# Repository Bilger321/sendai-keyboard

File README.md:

# sendai-keyboard
Just a little pet project of mine. Made using kiCAD.

Made with help from https://github.com/ruiqimao/keyboard-pcb-guide

Layout help was made with https://github.com/mechkeys/mechkeys

Code generated with http://kbfirmware.com/

Special Thanks to Jack @ https://github.com/qmk/qmk_firmware

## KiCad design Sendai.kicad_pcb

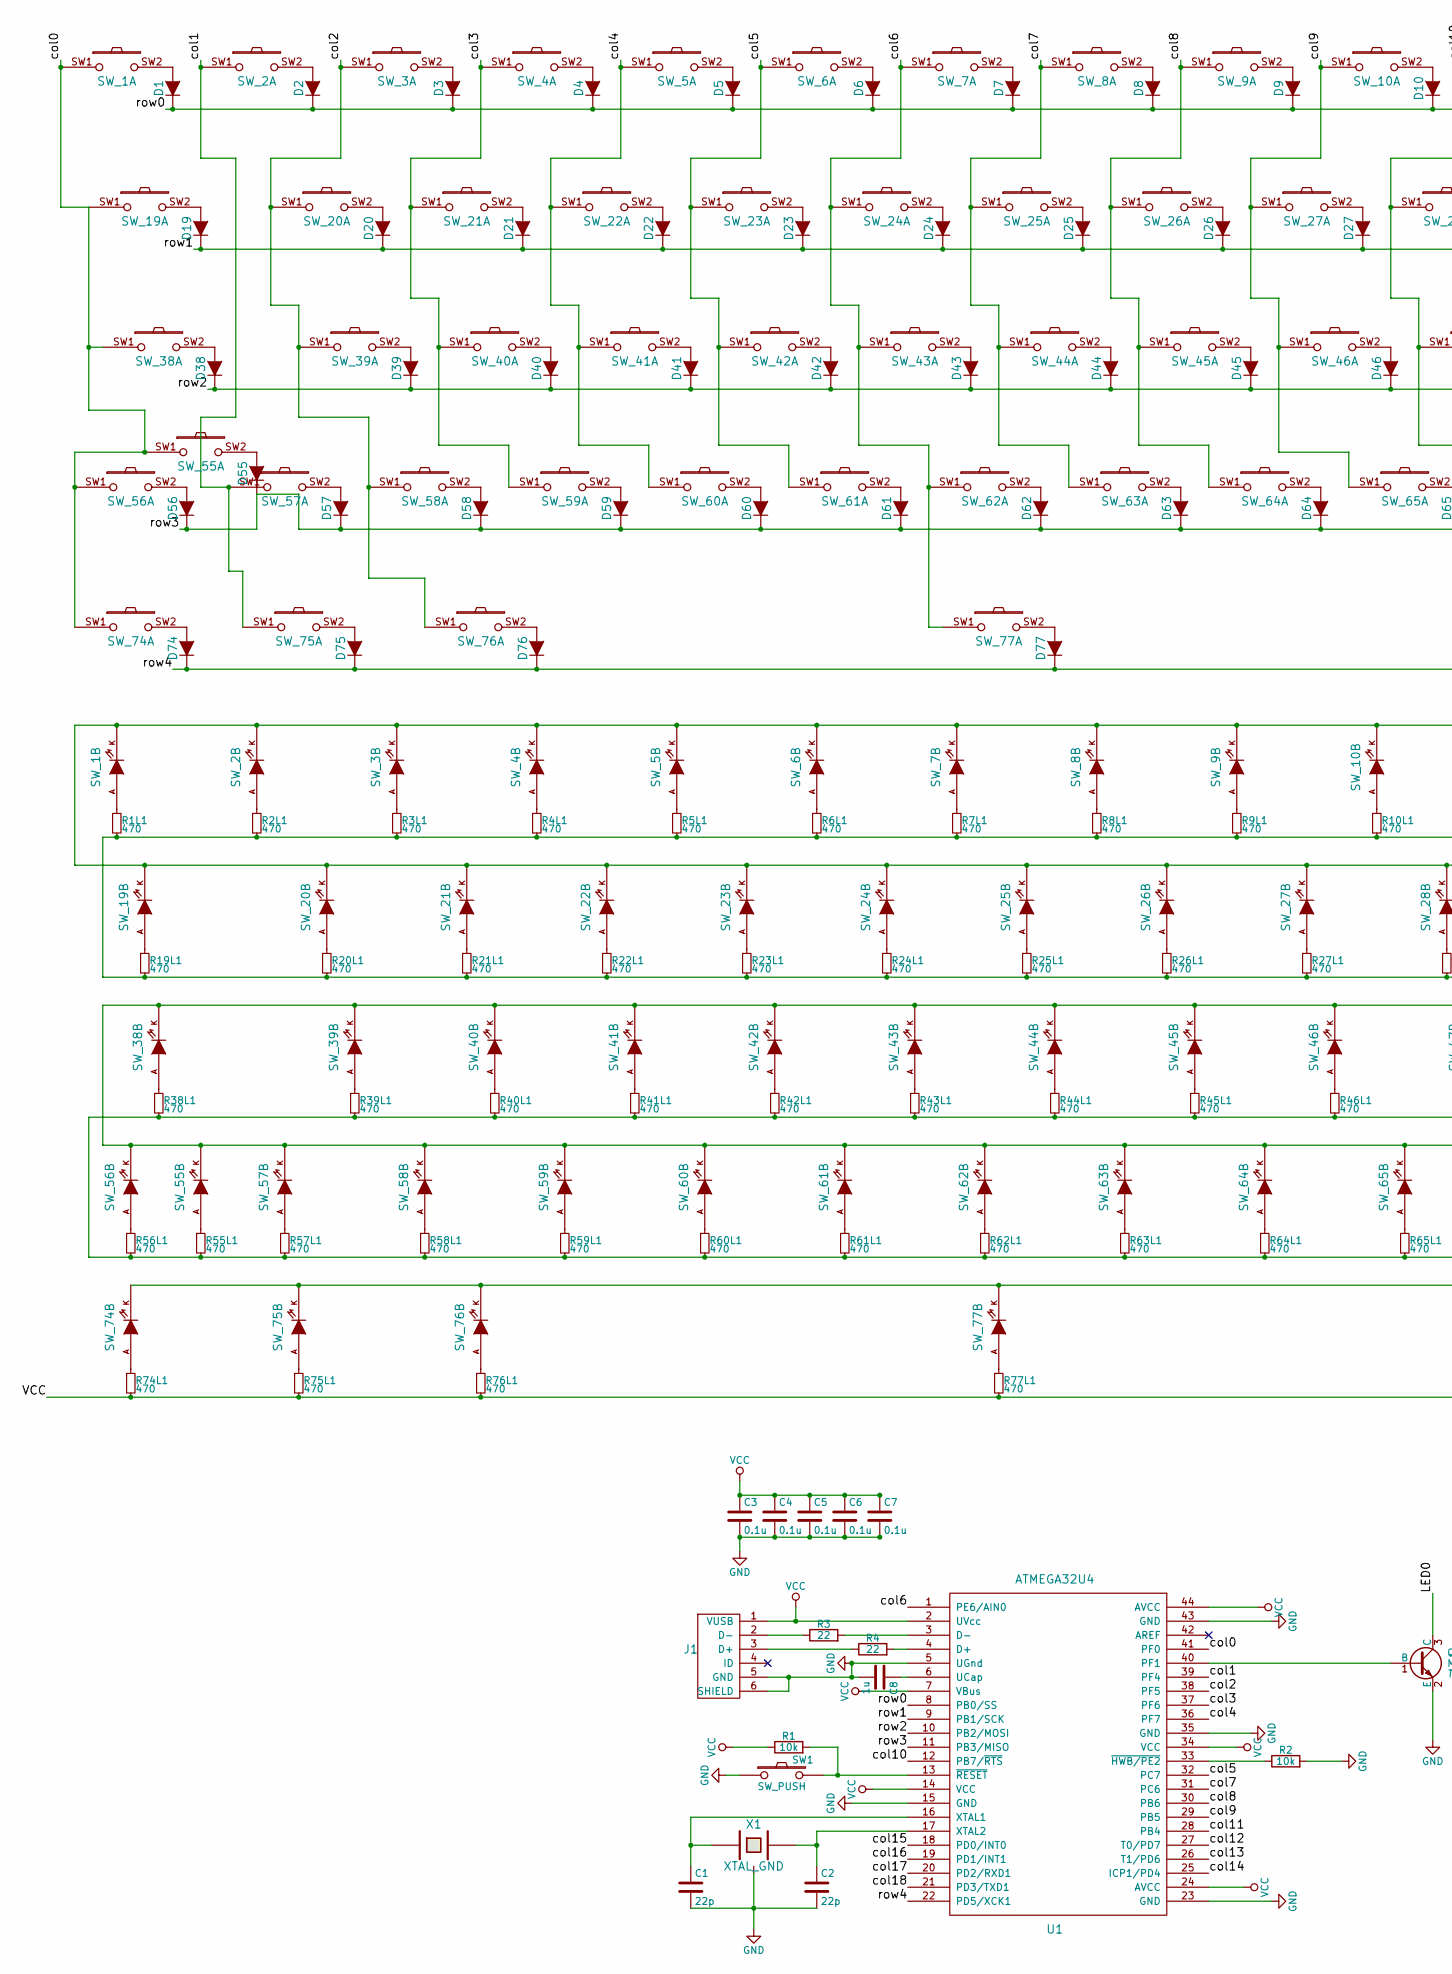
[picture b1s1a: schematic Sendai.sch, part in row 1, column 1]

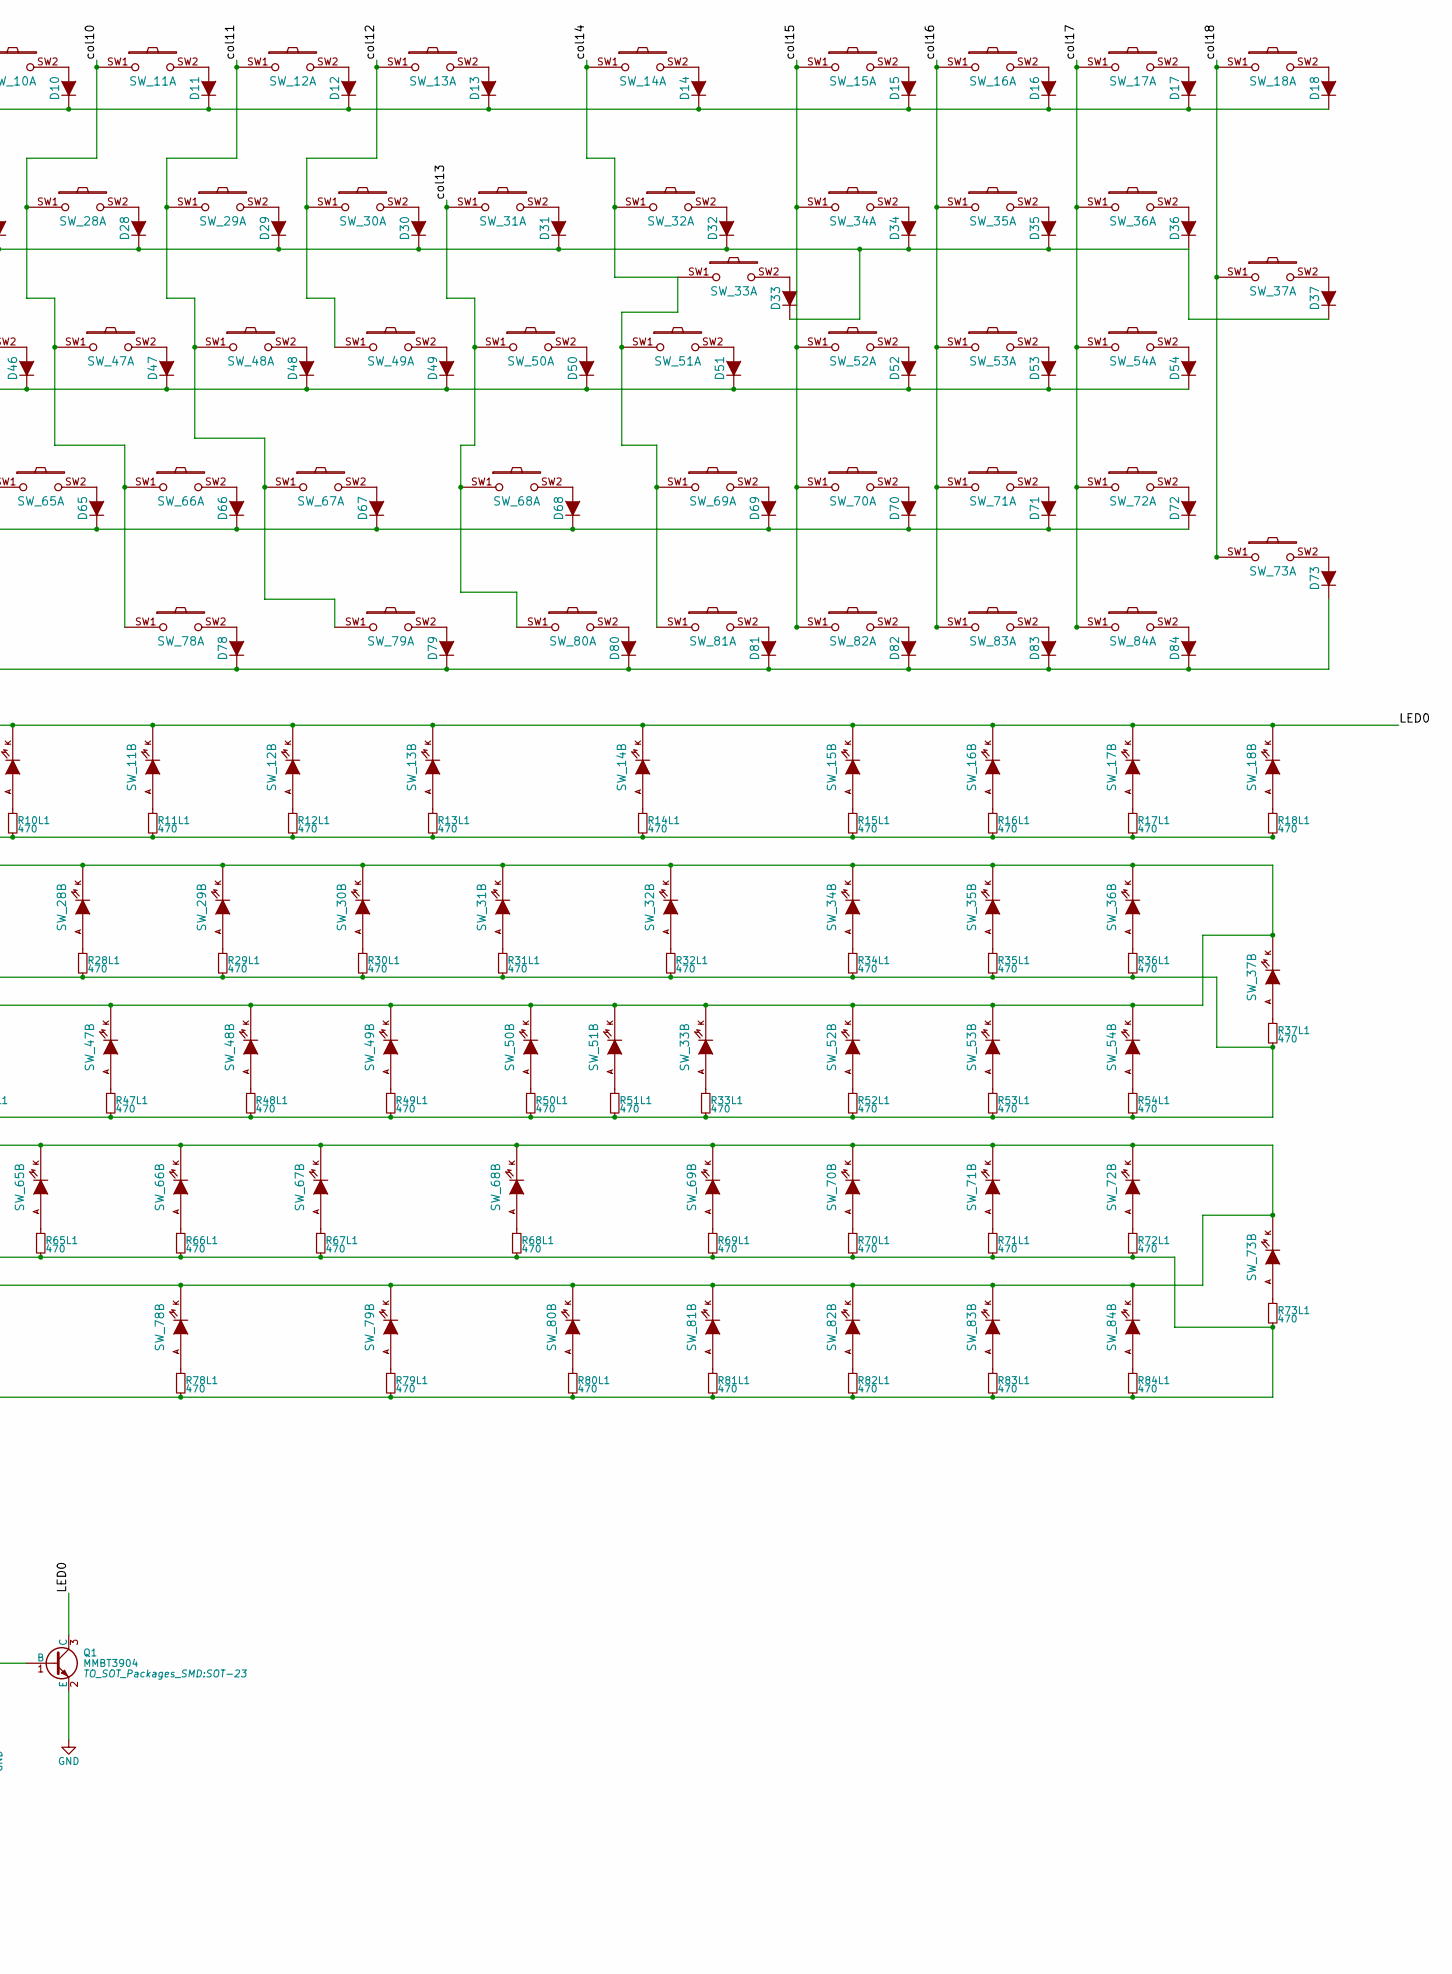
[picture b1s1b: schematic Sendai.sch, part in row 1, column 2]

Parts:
C1, C2: 22p; C_0805_HandSoldering
C3, C4, C5, C6, C7: 0.1u; C_0805_HandSoldering
C8: 1u; C_0805_HandSoldering
D1, D2, D3, D4, D5, D6, D7, D8, D9, D10, D11, D12, D13, D14, D15, D16, D17, D18, D19, D20, D21, D22, D23, D24, D25, D26, D27, D28, D29, D30, D31, D32, D33, D34, D35, D36, D37, D38, D39, D40, D41, D42, D43, D44, D45, D46, D47, D48, D49, D50, D51, D52, D53, D54, D55, D56, D57, D58, D59, D60, D61, D62, D63, D64, D65, D66, D67, D68, D69, D70, D71, D72, D73, D74, D75, D76, D77, D78, D79, D80, D81, D82, D83, D84: D; D_SOD123
J1: USB_mini_micro_B; USB_miniB_hirose_5S8
Q1: MMBT3904; SOT-23
R1, R2: 10k; R_0805_HandSoldering
R1L1, R2L1, R3L1, R4L1, R5L1, R6L1, R7L1, R8L1, R9L1, R10L1, R11L1, R12L1, R13L1, R14L1, R15L1, R16L1, R17L1, R18L1, R19L1, R20L1, R21L1, R22L1, R23L1, R24L1, R25L1, R26L1, R27L1, R28L1, R29L1, R30L1, R31L1, R32L1, R33L1, R34L1, R35L1, R36L1, R37L1, R38L1, R39L1, R40L1, R41L1, R42L1, R43L1, R44L1, R45L1, R46L1, R47L1, R48L1, R49L1, R50L1, R51L1, R52L1, R53L1, R54L1, R55L1, R56L1, R57L1, R58L1, R59L1, R60L1, R61L1, R62L1, R63L1, R64L1, R65L1, R66L1, R67L1, R68L1, R69L1, R70L1, R71L1, R72L1, R73L1, R74L1, R75L1, R76L1, R77L1, R78L1, R79L1, R80L1, R81L1, R82L1, R83L1, R84L1: 470; R_0805_HandSoldering
R3, R4: 22; R_0805_HandSoldering
SW1: SW_PUSH; SW_SPST_TL3342
SW_1, SW_2, SW_3, SW_4, SW_5, SW_6, SW_7, SW_8, SW_9, SW_10, SW_11, SW_12, SW_13, SW_14, SW_15, SW_16, SW_17, SW_18, SW_19, SW_20, SW_21, SW_22, SW_23, SW_24, SW_25, SW_26, SW_27, SW_28, SW_29, SW_30, SW_31, SW_32, SW_33, SW_34, SW_35, SW_36, SW_37, SW_38, SW_39, SW_40, SW_41, SW_42, SW_43, SW_44, SW_45, SW_46, SW_47, SW_48, SW_49, SW_50, SW_51, SW_52, SW_53, SW_54, SW_55, SW_56, SW_57, SW_58, SW_59, SW_60, SW_61, SW_62, SW_63, SW_64, SW_65, SW_66, SW_67, SW_68, SW_69, SW_70, SW_71, SW_72, SW_73, SW_74, SW_75, SW_76, SW_77, SW_78, SW_79, SW_80, SW_81, SW_82, SW_83, SW_84: MX_LED
U1: ATMEGA32U4; TQFP-44_10x10mm_Pitch0.8mm
X1: XTAL_GND; FA-238

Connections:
/LED0: Q1.3 (C), SW_1.K, SW_2.K, SW_3.K, SW_4.K, SW_5.K, SW_6.K, SW_7.K, SW_8.K, SW_9.K, SW_10.K, SW_11.K, SW_12.K, SW_13.K, SW_14.K, SW_15.K, SW_16.K, SW_17.K, SW_18.K, SW_19.K, SW_20.K, SW_21.K, SW_22.K, SW_23.K, SW_24.K, SW_25.K, SW_26.K, SW_27.K, SW_28.K, SW_29.K, SW_30.K, SW_31.K, SW_32.K, SW_33.K, SW_34.K, SW_35.K, SW_36.K, SW_37.K, SW_38.K, SW_39.K, SW_40.K, SW_41.K, SW_42.K, SW_43.K, SW_44.K, SW_45.K, SW_46.K, SW_47.K, SW_48.K, SW_49.K, SW_50.K, SW_51.K, SW_52.K, SW_53.K, SW_54.K, SW_55.K, SW_56.K, SW_57.K, SW_58.K, SW_59.K, SW_60.K, SW_61.K, SW_62.K, SW_63.K, SW_64.K, SW_65.K, SW_66.K, SW_67.K, SW_68.K, SW_69.K, SW_70.K, SW_71.K, SW_72.K, SW_73.K, SW_74.K, SW_75.K, SW_76.K, SW_77.K, SW_78.K, SW_79.K, SW_80.K, SW_81.K, SW_82.K, SW_83.K, SW_84.K
/col0: SW_1.SW1, SW_19.SW1, SW_38.SW1, SW_55.SW1, SW_56.SW1, SW_74.SW1, U1.41 (PF0)
/col1: SW_2.SW1, SW_57.SW1, SW_75.SW1, U1.39 (PF4)
/col2: SW_3.SW1, SW_20.SW1, SW_39.SW1, SW_58.SW1, SW_76.SW1, U1.38 (PF5)
/col3: SW_4.SW1, SW_21.SW1, SW_40.SW1, SW_59.SW1, U1.37 (PF6)
/col4: SW_5.SW1, SW_22.SW1, SW_41.SW1, SW_60.SW1, U1.36 (PF7)
/col5: SW_6.SW1, SW_23.SW1, SW_42.SW1, SW_61.SW1, U1.32 (PC7)
/col6: SW_7.SW1, SW_24.SW1, SW_43.SW1, SW_62.SW1, SW_77.SW1, U1.1 (PE6/AIN0)
/col7: SW_8.SW1, SW_25.SW1, SW_44.SW1, SW_63.SW1, U1.31 (PC6)
/col8: SW_9.SW1, SW_26.SW1, SW_45.SW1, SW_64.SW1, U1.30 (PB6)
/col9: SW_10.SW1, SW_27.SW1, SW_46.SW1, SW_65.SW1, U1.29 (PB5)
/col10: SW_11.SW1, SW_28.SW1, SW_47.SW1, SW_66.SW1, SW_78.SW1, U1.12 (PB7/~RTS)
/col11: SW_12.SW1, SW_29.SW1, SW_48.SW1, SW_67.SW1, SW_79.SW1, U1.28 (PB4)
/col12: SW_13.SW1, SW_30.SW1, SW_49.SW1, U1.27 (T0/PD7)
/col13: SW_31.SW1, SW_50.SW1, SW_68.SW1, SW_80.SW1, U1.26 (T1/PD6)
/col14: SW_14.SW1, SW_32.SW1, SW_33.SW1, SW_51.SW1, SW_69.SW1, SW_81.SW1, U1.25 (ICP1/PD4)
/col15: SW_15.SW1, SW_34.SW1, SW_52.SW1, SW_70.SW1, SW_82.SW1, U1.18 (PD0/INT0)
/col16: SW_16.SW1, SW_35.SW1, SW_53.SW1, SW_71.SW1, SW_83.SW1, U1.19 (PD1/INT1)
/col17: SW_17.SW1, SW_36.SW1, SW_54.SW1, SW_72.SW1, SW_84.SW1, U1.20 (PD2/RXD1)
/col18: SW_18.SW1, SW_37.SW1, SW_73.SW1, U1.21 (PD3/TXD1)
/row0: D1.1 (K), D2.1 (K), D3.1 (K), D4.1 (K), D5.1 (K), D6.1 (K), D7.1 (K), D8.1 (K), D9.1 (K), D10.1 (K), D11.1 (K), D12.1 (K), D13.1 (K), D14.1 (K), D15.1 (K), D16.1 (K), D17.1 (K), D18.1 (K), U1.8 (PB0/SS)
/row1: D19.1 (K), D20.1 (K), D21.1 (K), D22.1 (K), D23.1 (K), D24.1 (K), D25.1 (K), D26.1 (K), D27.1 (K), D28.1 (K), D29.1 (K), D30.1 (K), D31.1 (K), D32.1 (K), D33.1 (K), D34.1 (K), D35.1 (K), D36.1 (K), D37.1 (K), U1.9 (PB1/SCK)
/row2: D38.1 (K), D39.1 (K), D40.1 (K), D41.1 (K), D42.1 (K), D43.1 (K), D44.1 (K), D45.1 (K), D46.1 (K), D47.1 (K), D48.1 (K), D49.1 (K), D50.1 (K), D51.1 (K), D52.1 (K), D53.1 (K), D54.1 (K), U1.10 (PB2/MOSI)
/row3: D55.1 (K), D56.1 (K), D57.1 (K), D58.1 (K), D59.1 (K), D60.1 (K), D61.1 (K), D62.1 (K), D63.1 (K), D64.1 (K), D65.1 (K), D66.1 (K), D67.1 (K), D68.1 (K), D69.1 (K), D70.1 (K), D71.1 (K), D72.1 (K), U1.11 (PB3/MISO)
/row4: D73.1 (K), D74.1 (K), D75.1 (K), D76.1 (K), D77.1 (K), D78.1 (K), D79.1 (K), D80.1 (K), D81.1 (K), D82.1 (K), D83.1 (K), D84.1 (K), U1.22 (PD5/XCK1)
GND: C1.2, C2.2, C3.2, C4.2, C5.2, C6.2, C7.2, C8.2, J1.5 (GND), J1.6 (SHIELD), Q1.2 (E), R2.2, SW1.1, U1.5 (UGnd), U1.15 (GND), U1.23 (GND), U1.35 (GND), U1.43 (GND), X1.3
unnamed: C1.1, U1.16 (XTAL1), X1.1
unnamed: C2.1, U1.17 (XTAL2), X1.2
unnamed: C8.1, U1.6 (UCap)
unnamed: D1.2 (A), SW_1.SW2
unnamed: D2.2 (A), SW_2.SW2
unnamed: D3.2 (A), SW_3.SW2
unnamed: D4.2 (A), SW_4.SW2
unnamed: D5.2 (A), SW_5.SW2
unnamed: D6.2 (A), SW_6.SW2
unnamed: D7.2 (A), SW_7.SW2
unnamed: D8.2 (A), SW_8.SW2
unnamed: D9.2 (A), SW_9.SW2
unnamed: D10.2 (A), SW_10.SW2
unnamed: D11.2 (A), SW_11.SW2
unnamed: D12.2 (A), SW_12.SW2
unnamed: D13.2 (A), SW_13.SW2
unnamed: D14.2 (A), SW_14.SW2
unnamed: D15.2 (A), SW_15.SW2
unnamed: D16.2 (A), SW_16.SW2
unnamed: D17.2 (A), SW_17.SW2
unnamed: D18.2 (A), SW_18.SW2
unnamed: D19.2 (A), SW_19.SW2
unnamed: D20.2 (A), SW_20.SW2
unnamed: D21.2 (A), SW_21.SW2
unnamed: D22.2 (A), SW_22.SW2
unnamed: D23.2 (A), SW_23.SW2
unnamed: D24.2 (A), SW_24.SW2
unnamed: D25.2 (A), SW_25.SW2
unnamed: D26.2 (A), SW_26.SW2
unnamed: D27.2 (A), SW_27.SW2
unnamed: D28.2 (A), SW_28.SW2
unnamed: D29.2 (A), SW_29.SW2
unnamed: D30.2 (A), SW_30.SW2
unnamed: D31.2 (A), SW_31.SW2
unnamed: D32.2 (A), SW_32.SW2
unnamed: D33.2 (A), SW_33.SW2
unnamed: D34.2 (A), SW_34.SW2
unnamed: D35.2 (A), SW_35.SW2
unnamed: D36.2 (A), SW_36.SW2
unnamed: D37.2 (A), SW_37.SW2
unnamed: D38.2 (A), SW_38.SW2
unnamed: D39.2 (A), SW_39.SW2
unnamed: D40.2 (A), SW_40.SW2
unnamed: D41.2 (A), SW_41.SW2
unnamed: D42.2 (A), SW_42.SW2
unnamed: D43.2 (A), SW_43.SW2
unnamed: D44.2 (A), SW_44.SW2
unnamed: D45.2 (A), SW_45.SW2
unnamed: D46.2 (A), SW_46.SW2
unnamed: D47.2 (A), SW_47.SW2
unnamed: D48.2 (A), SW_48.SW2
unnamed: D49.2 (A), SW_49.SW2
unnamed: D50.2 (A), SW_50.SW2
unnamed: D51.2 (A), SW_51.SW2
unnamed: D52.2 (A), SW_52.SW2
unnamed: D53.2 (A), SW_53.SW2
unnamed: D54.2 (A), SW_54.SW2
unnamed: D55.2 (A), SW_55.SW2
unnamed: D56.2 (A), SW_56.SW2
unnamed: D57.2 (A), SW_57.SW2
unnamed: D58.2 (A), SW_58.SW2
unnamed: D59.2 (A), SW_59.SW2
unnamed: D60.2 (A), SW_60.SW2
unnamed: D61.2 (A), SW_61.SW2
unnamed: D62.2 (A), SW_62.SW2
unnamed: D63.2 (A), SW_63.SW2
unnamed: D64.2 (A), SW_64.SW2
unnamed: D65.2 (A), SW_65.SW2
unnamed: D66.2 (A), SW_66.SW2
unnamed: D67.2 (A), SW_67.SW2
unnamed: D68.2 (A), SW_68.SW2
unnamed: D69.2 (A), SW_69.SW2
unnamed: D70.2 (A), SW_70.SW2
unnamed: D71.2 (A), SW_71.SW2
unnamed: D72.2 (A), SW_72.SW2
unnamed: D73.2 (A), SW_73.SW2
unnamed: D74.2 (A), SW_74.SW2
unnamed: D75.2 (A), SW_75.SW2
unnamed: D76.2 (A), SW_76.SW2
unnamed: D77.2 (A), SW_77.SW2
unnamed: D78.2 (A), SW_78.SW2
unnamed: D79.2 (A), SW_79.SW2
unnamed: D80.2 (A), SW_80.SW2
unnamed: D81.2 (A), SW_81.SW2
unnamed: D82.2 (A), SW_82.SW2
unnamed: D83.2 (A), SW_83.SW2
unnamed: D84.2 (A), SW_84.SW2
unnamed: J1.2 (D-), R3.1
unnamed: J1.3 (D+), R4.1
unnamed: Q1.1 (B), U1.40 (PF1)
unnamed: R1.2, SW1.2, U1.13 (~RESET)
unnamed: R1L1.1, SW_1.A
unnamed: R2.1, U1.33 (~HWB/PE2)
unnamed: R2L1.1, SW_2.A
unnamed: R3.2, U1.3 (D-)
unnamed: R3L1.1, SW_3.A
unnamed: R4.2, U1.4 (D+)
unnamed: R4L1.1, SW_4.A
unnamed: R5L1.1, SW_5.A
unnamed: R6L1.1, SW_6.A
unnamed: R7L1.1, SW_7.A
unnamed: R8L1.1, SW_8.A
unnamed: R9L1.1, SW_9.A
unnamed: R10L1.1, SW_10.A
unnamed: R11L1.1, SW_11.A
unnamed: R12L1.1, SW_12.A
unnamed: R13L1.1, SW_13.A
unnamed: R14L1.1, SW_14.A
unnamed: R15L1.1, SW_15.A
unnamed: R16L1.1, SW_16.A
unnamed: R17L1.1, SW_17.A
unnamed: R18L1.1, SW_18.A
unnamed: R19L1.1, SW_19.A
unnamed: R20L1.1, SW_20.A
unnamed: R21L1.1, SW_21.A
unnamed: R22L1.1, SW_22.A
unnamed: R23L1.1, SW_23.A
unnamed: R24L1.1, SW_24.A
unnamed: R25L1.1, SW_25.A
unnamed: R26L1.1, SW_26.A
unnamed: R27L1.1, SW_27.A
unnamed: R28L1.1, SW_28.A
unnamed: R29L1.1, SW_29.A
unnamed: R30L1.1, SW_30.A
unnamed: R31L1.1, SW_31.A
unnamed: R32L1.1, SW_32.A
unnamed: R33L1.1, SW_33.A
unnamed: R34L1.1, SW_34.A
unnamed: R35L1.1, SW_35.A
unnamed: R36L1.1, SW_36.A
unnamed: R37L1.1, SW_37.A
unnamed: R38L1.1, SW_38.A
unnamed: R39L1.1, SW_39.A
unnamed: R40L1.1, SW_40.A
unnamed: R41L1.1, SW_41.A
unnamed: R42L1.1, SW_42.A
unnamed: R43L1.1, SW_43.A
unnamed: R44L1.1, SW_44.A
unnamed: R45L1.1, SW_45.A
unnamed: R46L1.1, SW_46.A
unnamed: R47L1.1, SW_47.A
unnamed: R48L1.1, SW_48.A
unnamed: R49L1.1, SW_49.A
unnamed: R50L1.1, SW_50.A
unnamed: R51L1.1, SW_51.A
unnamed: R52L1.1, SW_52.A
unnamed: R53L1.1, SW_53.A
unnamed: R54L1.1, SW_54.A
unnamed: R55L1.1, SW_55.A
unnamed: R56L1.1, SW_56.A
unnamed: R57L1.1, SW_57.A
unnamed: R58L1.1, SW_58.A
unnamed: R59L1.1, SW_59.A
unnamed: R60L1.1, SW_60.A
unnamed: R61L1.1, SW_61.A
unnamed: R62L1.1, SW_62.A
unnamed: R63L1.1, SW_63.A
unnamed: R64L1.1, SW_64.A
unnamed: R65L1.1, SW_65.A
unnamed: R66L1.1, SW_66.A
unnamed: R67L1.1, SW_67.A
unnamed: R68L1.1, SW_68.A
unnamed: R69L1.1, SW_69.A
unnamed: R70L1.1, SW_70.A
unnamed: R71L1.1, SW_71.A
unnamed: R72L1.1, SW_72.A
unnamed: R73L1.1, SW_73.A
unnamed: R74L1.1, SW_74.A
unnamed: R75L1.1, SW_75.A
unnamed: R76L1.1, SW_76.A
unnamed: R77L1.1, SW_77.A
unnamed: R78L1.1, SW_78.A
unnamed: R79L1.1, SW_79.A
unnamed: R80L1.1, SW_80.A
unnamed: R81L1.1, SW_81.A
unnamed: R82L1.1, SW_82.A
unnamed: R83L1.1, SW_83.A
unnamed: R84L1.1, SW_84.A
VCC: C3.1, C4.1, C5.1, C6.1, C7.1, J1.1 (VUSB), R1.1, R1L1.2, R2L1.2, R3L1.2, R4L1.2, R5L1.2, R6L1.2, R7L1.2, R8L1.2, R9L1.2, R10L1.2, R11L1.2, R12L1.2, R13L1.2, R14L1.2, R15L1.2, R16L1.2, R17L1.2, R18L1.2, R19L1.2, R20L1.2, R21L1.2, R22L1.2, R23L1.2, R24L1.2, R25L1.2, R26L1.2, R27L1.2, R28L1.2, R29L1.2, R30L1.2, R31L1.2, R32L1.2, R33L1.2, R34L1.2, R35L1.2, R36L1.2, R37L1.2, R38L1.2, R39L1.2, R40L1.2, R41L1.2, R42L1.2, R43L1.2, R44L1.2, R45L1.2, R46L1.2, R47L1.2, R48L1.2, R49L1.2, R50L1.2, R51L1.2, R52L1.2, R53L1.2, R54L1.2, R55L1.2, R56L1.2, R57L1.2, R58L1.2, R59L1.2, R60L1.2, R61L1.2, R62L1.2, R63L1.2, R64L1.2, R65L1.2, R66L1.2, R67L1.2, R68L1.2, R69L1.2, R70L1.2, R71L1.2, R72L1.2, R73L1.2, R74L1.2, R75L1.2, R76L1.2, R77L1.2, R78L1.2, R79L1.2, R80L1.2, R81L1.2, R82L1.2, R83L1.2, R84L1.2, U1.2 (UVcc), U1.7 (VBus), U1.14 (VCC), U1.24 (AVCC), U1.34 (VCC), U1.44 (AVCC)

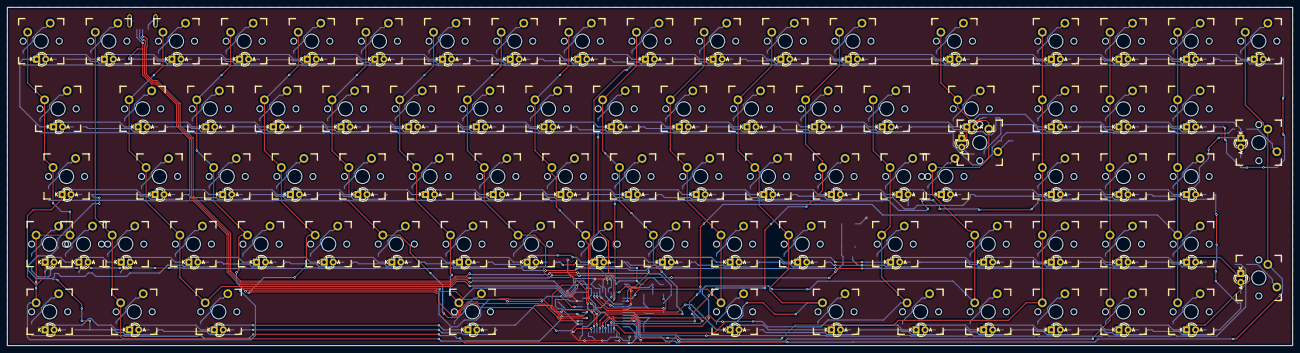
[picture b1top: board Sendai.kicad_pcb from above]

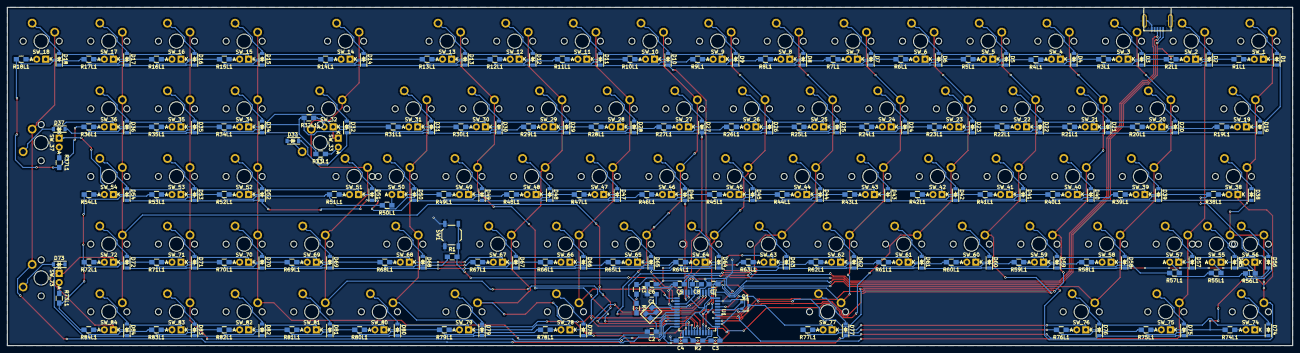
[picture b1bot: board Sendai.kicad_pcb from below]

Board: 2 copper layers, 361.9 x 95.2 mm, 269 parts (185 on the bottom side), 205 nets.

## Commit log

2018-02-13 First commit
    Keyboard PCB developed for US/UK layout.
    Made with help from https://github.com/ruiqimao/keyboard-pcb-guide
    Layout help was made with https://github.com/mechkeys/mechkeys
    Code generated with http://kbfirmware.com/
    Special Thanks to Jack @ https://github.com/qmk/qmk_firmware
